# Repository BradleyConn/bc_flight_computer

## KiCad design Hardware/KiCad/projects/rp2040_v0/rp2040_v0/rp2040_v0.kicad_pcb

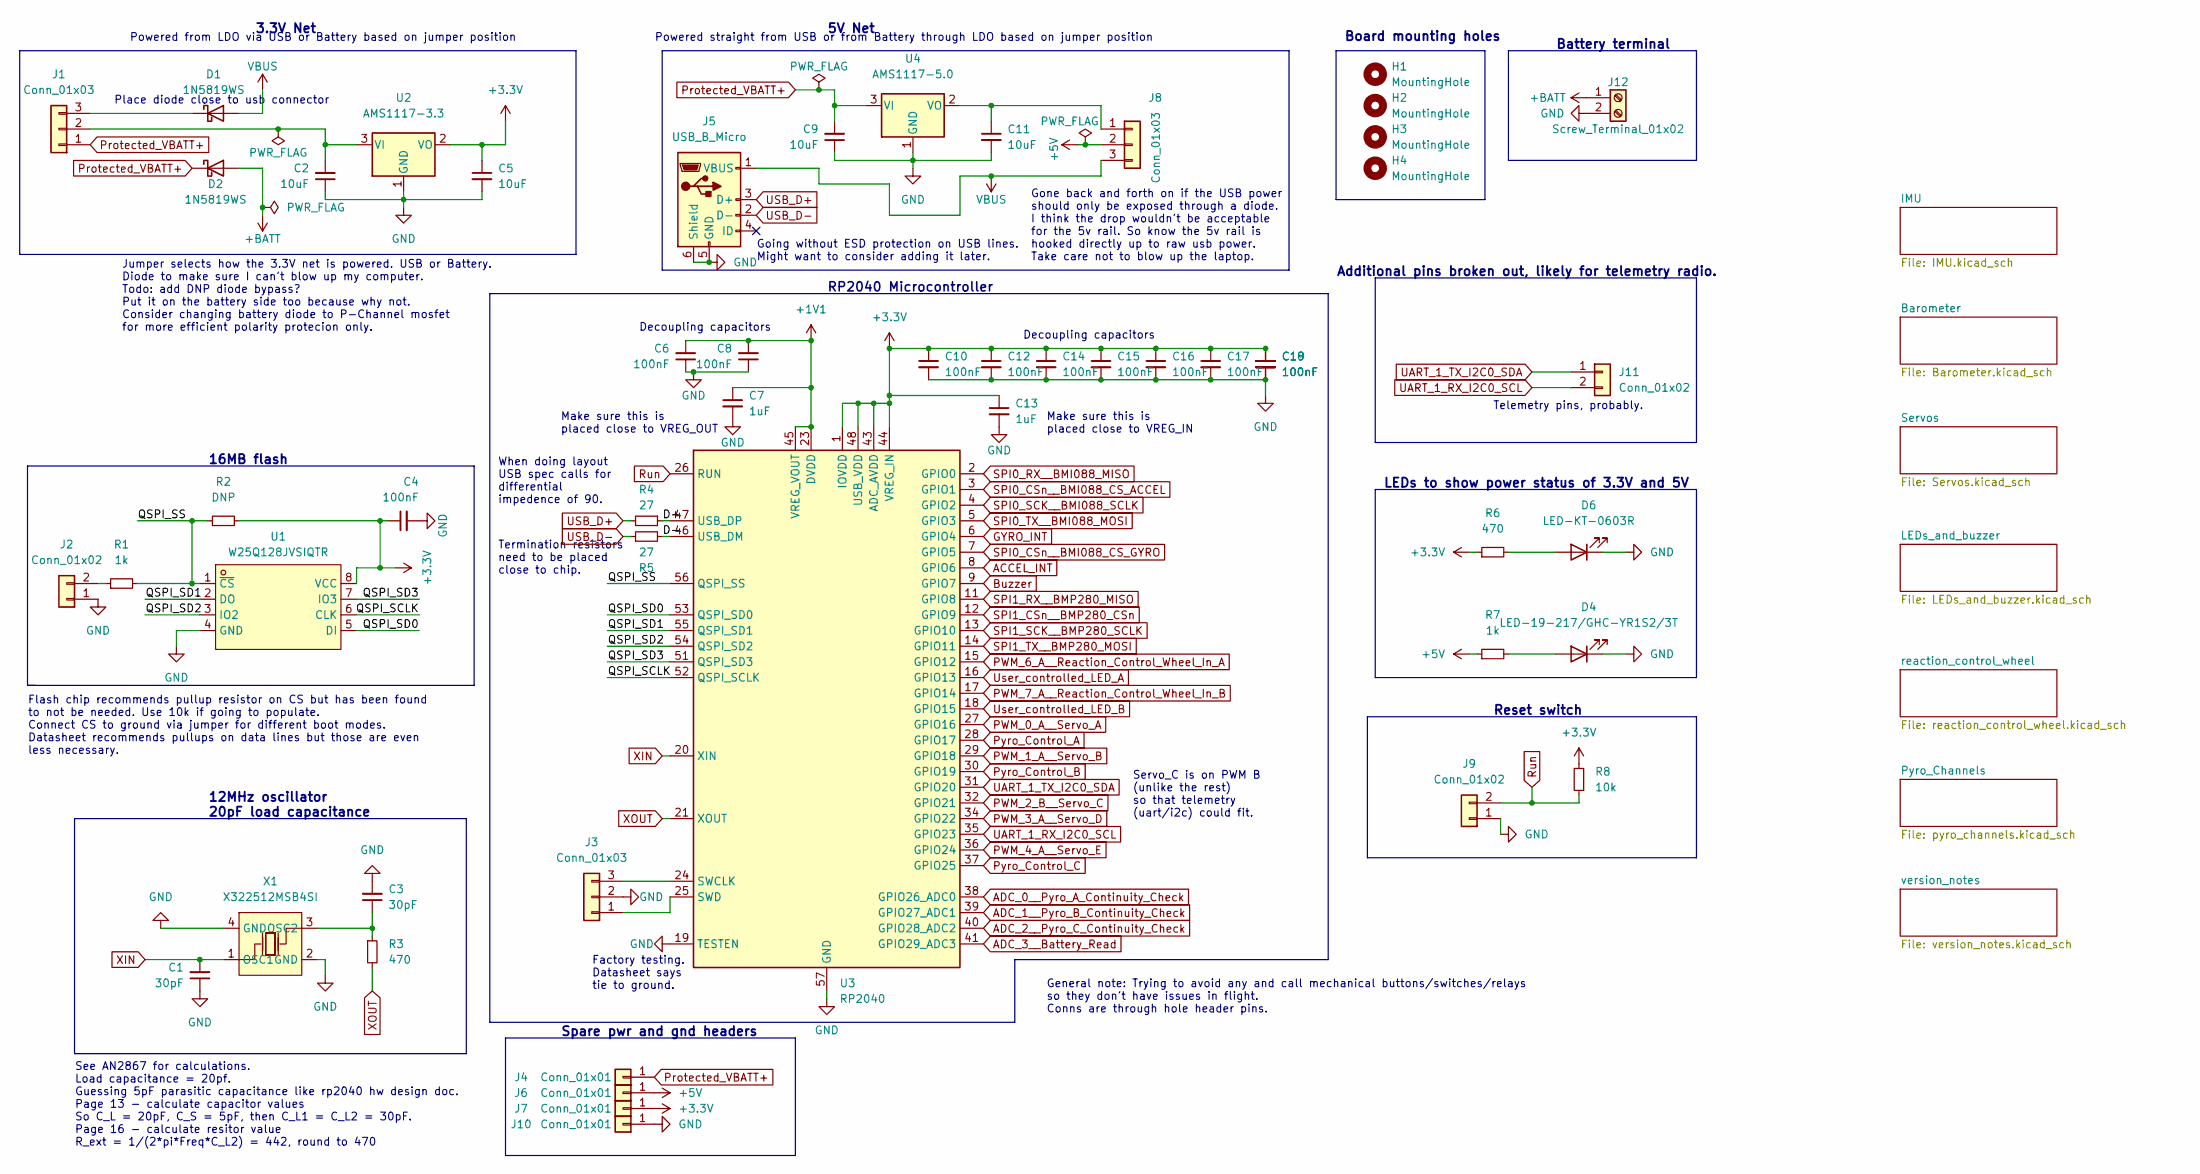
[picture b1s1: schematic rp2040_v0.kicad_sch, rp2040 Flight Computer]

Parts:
C1, C3: 30pF; C_0402_1005Metric; LCSC Part C1570
C2, C5, C9, C11: 10uF; C_0805_2012Metric; LCSC Part C15850
C4, C6, C8, C10, C12, C14, C15, C16, C17, C18, C19: 100nF; C_0402_1005Metric; LCSC Part C307331
C7, C13: 1uF; C_0402_1005Metric; LCSC Part C52923
D1, D2: 1N5819WS; D_SOD-323; LCSC Part C191023
D4: LED-19-217/GHC-YR1S2/3T; LED_0603_1608Metric; LCSC Part C72043
D6: LED-KT-0603R; LED_0603_1608Metric; LCSC Part C2286
H1, H2, H3, H4: MountingHole; MountingHole_2mm
J1, J3, J8: Conn_01x03; PinHeader_1x03_P2.54mm_Vertical
J2, J9, J11: Conn_01x02; PinHeader_1x02_P2.54mm_Vertical
J4, J6, J7, J10: Conn_01x01; PinHeader_1x01_P2.54mm_Vertical
J5: USB_B_Micro; MICRO-USB-SMD_MICROXNJ; LCSC Part C404969
J12: Screw_Terminal_01x02; CONN-TH_XY301V-A-5.0-2P; JLC Part Extended Part
R1, R7: 1k; R_0402_1005Metric; LCSC Part C11702
R2: DNP; R_0402_1005Metric
R3, R6: 470; R_0402_1005Metric; LCSC Part C25117
R4, R5: 27; R_0603_1608Metric; LCSC Part C25190
R8: 10k; R_0402_1005Metric; LCSC Part C25744
U1: W25Q128JVSIQTR; SOIC-8_5.23x5.23mm_P1.27mm; LCSC Part C97521
U2: AMS1117-3.3; SOT-223-3_TabPin2; LCSC Part C6186
U3: RP2040; LQFN-56_L7.0-W7.0-P0.4-EP; JLC Part Extended Part
U4: AMS1117-5.0; SOT-223-3_TabPin2; LCSC Part C6187
X1: X322512MSB4SI; OSC-SMD_4P-L3.2-W2.5-BL; LCSC Part C9002

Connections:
+1V1: C6.2, C7.1, C8.2, U3.23 (DVDD), U3.45 (VREG_VOUT), U3.50 (DVDD)
+3.3V: C4.1, C5.1, C10.1, C12.1, C13.1, C14.1, C15.1, C16.1, C17.1, C18.1, C19.1, J7.1, R2.2, R6.1, R8.2, U1.8 (VCC), U2.2 (VO), U3.1 (IOVDD), U3.10 (IOVDD), U3.22 (IOVDD), U3.33 (IOVDD), U3.42 (IOVDD), U3.43 (ADC_AVDD), U3.44 (VREG_IN), U3.48 (USB_VDD), U3.49 (IOVDD); also elsewhere on the board
+5V: J6.1, J8.2, R7.1; also elsewhere on the board
+BATT: D2.2 (A), J12.1; also elsewhere on the board
/D+: R4.1, U3.47 (USB_DP)
/D-: R5.2, U3.46 (USB_DM)
/QSPI_SCLK: U1.6 (CLK), U3.52 (QSPI_SCLK)
/QSPI_SD0: U1.5 (DI), U3.53 (QSPI_SD0)
/QSPI_SD1: U1.2 (DO), U3.55 (QSPI_SD1)
/QSPI_SD2: U1.3 (IO2), U3.54 (QSPI_SD2)
/QSPI_SD3: U1.7 (IO3), U3.51 (QSPI_SD3)
/QSPI_SS: R1.2, R2.1, U1.1 (~CS), U3.56 (QSPI_SS)
ACCEL_INT: U3.8 (GPIO6); also elsewhere on the board
ADC_0__Pyro_A_Continuity_Check: U3.38 (GPIO26_ADC0); also elsewhere on the board
ADC_1__Pyro_B_Continuity_Check: U3.39 (GPIO27_ADC1); also elsewhere on the board
ADC_2__Pyro_C_Continuity_Check: U3.40 (GPIO28_ADC2); also elsewhere on the board
ADC_3__Battery_Read: U3.41 (GPIO29_ADC3); also elsewhere on the board
Buzzer: U3.9 (GPIO7); also elsewhere on the board
GND: C1.1, C2.1, C3.2, C4.2, C5.2, C6.1, C7.2, C8.1, C9.1, C10.2, C11.2, C12.2, C13.2, C14.2, C15.2, C16.2, C17.2, C18.2, C19.2, D4.1 (K), D6.1 (K), J2.1, J3.2, J5.5 (GND), J5.6 (Shield), J9.1, J10.1, J12.2, U1.4 (GND), U2.1 (GND), U3.19 (TESTEN), U3.57 (GND), U4.1 (GND), X1.2 (GND), X1.4 (GND); also elsewhere on the board
GYRO_INT: U3.6 (GPIO4); also elsewhere on the board
unnamed: C2.2, J1.2, U2.3 (VI)
unnamed: C3.1, R3.1, X1.3 (OSC2)
unnamed: C11.1, J8.1, U4.2 (VO)
unnamed: D1.1 (K), J1.3
unnamed: D4.2 (A), R7.2
unnamed: D6.2 (A), R6.2
unnamed: J2.2, R1.1
unnamed: J3.1, U3.25 (SWD)
unnamed: J3.3, U3.24 (SWCLK)
PWM_0_A__Servo_A: U3.27 (GPIO16); also elsewhere on the board
PWM_1_A__Servo_B: U3.29 (GPIO18); also elsewhere on the board
PWM_2_B__Servo_C: U3.32 (GPIO21); also elsewhere on the board
PWM_3_A__Servo_D: U3.34 (GPIO22); also elsewhere on the board
PWM_4_A__Servo_E: U3.36 (GPIO24); also elsewhere on the board
PWM_6_A__Reaction_Control_Wheel_In_A: U3.15 (GPIO12); also elsewhere on the board
PWM_7_A__Reaction_Control_Wheel_In_B: U3.17 (GPIO14); also elsewhere on the board
Protected_VBATT+: C9.2, D2.1 (K), J1.1, J4.1, U4.3 (VI); also elsewhere on the board
Pyro_Control_A: U3.28 (GPIO17); also elsewhere on the board
Pyro_Control_B: U3.30 (GPIO19); also elsewhere on the board
Pyro_Control_C: U3.37 (GPIO25); also elsewhere on the board
Run: J9.2, R8.1, U3.26 (RUN)
SPI0_CSn__BMI088_CS_ACCEL: U3.3 (GPIO1); also elsewhere on the board
SPI0_CSn__BMI088_CS_GYRO: U3.7 (GPIO5); also elsewhere on the board
SPI0_RX__BMI088_MISO: U3.2 (GPIO0); also elsewhere on the board
SPI0_SCK__BMI088_SCLK: U3.4 (GPIO2); also elsewhere on the board
SPI0_TX__BMI088_MOSI: U3.5 (GPIO3); also elsewhere on the board
SPI1_CSn__BMP280_CSn: U3.12 (GPIO9); also elsewhere on the board
SPI1_RX__BMP280_MISO: U3.11 (GPIO8); also elsewhere on the board
SPI1_SCK__BMP280_SCLK: U3.13 (GPIO10); also elsewhere on the board
SPI1_TX__BMP280_MOSI: U3.14 (GPIO11); also elsewhere on the board
UART_1_RX_I2C0_SCL: J11.2, U3.35 (GPIO23)
UART_1_TX_I2C0_SDA: J11.1, U3.31 (GPIO20)
USB_D+: J5.3 (D+), R4.2
USB_D-: J5.2 (D-), R5.1
User_controlled_LED_A: U3.16 (GPIO13); also elsewhere on the board
User_controlled_LED_B: U3.18 (GPIO15); also elsewhere on the board
VBUS: D1.2 (A), J5.1 (VBUS), J8.3
XIN: C1.2, U3.20 (XIN), X1.1 (OSC1)
XOUT: R3.2, U3.21 (XOUT)

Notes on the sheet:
Jumper selects how the 3.3V net is powered. USB or Battery. Diode to make sure I can't blow up my computer. Todo: add DNP diode bypass? Put it on the battery side too because why not. Consider changing battery diode to P-Channel mosfet for more efficient polarity protecion only.
Termination resistors need to be placed close to chip.
Telemetry pins, probably.
Make sure this is placed close to VREG_OUT
Servo_C is on PWM B (unlike the rest) so that telemetry (uart/i2c) could fit.
Flash chip recommends pullup resistor on CS but has been found to not be needed. Use 10k if going to populate. Connect CS to ground via jumper for different boot modes. Datasheet recommends pullups on data lines but those are even less necessary.
Factory testing. Datasheet says tie to ground.
3.3V Net
16MB flash
Board mounting holes
Battery terminal
Additional pins broken out, likely for telemetry radio.
Reset switch
When doing layout USB spec calls for differential impedence of 90.
Make sure this is placed close to VREG_IN
Gone back and forth on if the USB power should only be exposed through a diode. I think the drop wouldn't be acceptable for the 5v rail. So know the 5v rail is hooked directly up to raw usb power. Take care not to blow up the laptop.
Place diode close to usb connector
See AN2867 for calculations. Load capacitance = 20pf. Guessing 5pF parasitic capacitance like rp2040 hw design doc. Page 13 - calculate capacitor values So C_L = 20pF, C_S = 5pF, then C_L1 = C_L2 = 30pF. Page 16 - calculate resitor value R_ext = 1/(2*pi*Freq*C_L2) = 442, round to 470
5V Net
Going without ESD protection on USB lines. Might want to consider adding it later.
RP2040 Microcontroller
General note: Trying to avoid any and call mechanical buttons/switches/relays so they don't have issues in flight. Conns are through hole header pins.
Spare pwr and gnd headers
Powered straight from USB or from Battery through LDO based on jumper position
Decoupling capacitors
Powered from LDO via USB or Battery based on jumper position
12MHz oscillator 20pF load capacitance
LEDs to show power status of 3.3V and 5V

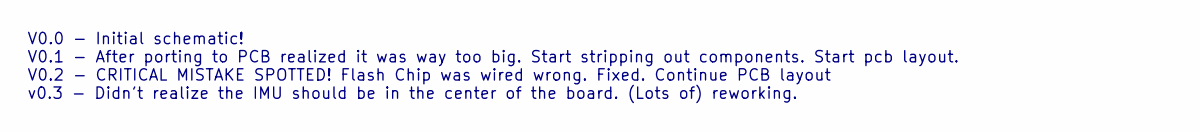
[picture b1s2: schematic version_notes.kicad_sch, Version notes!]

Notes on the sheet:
V0.0 - Initial schematic! V0.1 - After porting to PCB realized it was way too big. Start stripping out components. Start pcb layout. V0.2 - CRITICAL MISTAKE SPOTTED! Flash Chip was wired wrong. Fixed. Continue PCB layout v0.3 - Didn't realize the IMU should be in the center of the board. (Lots of) 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

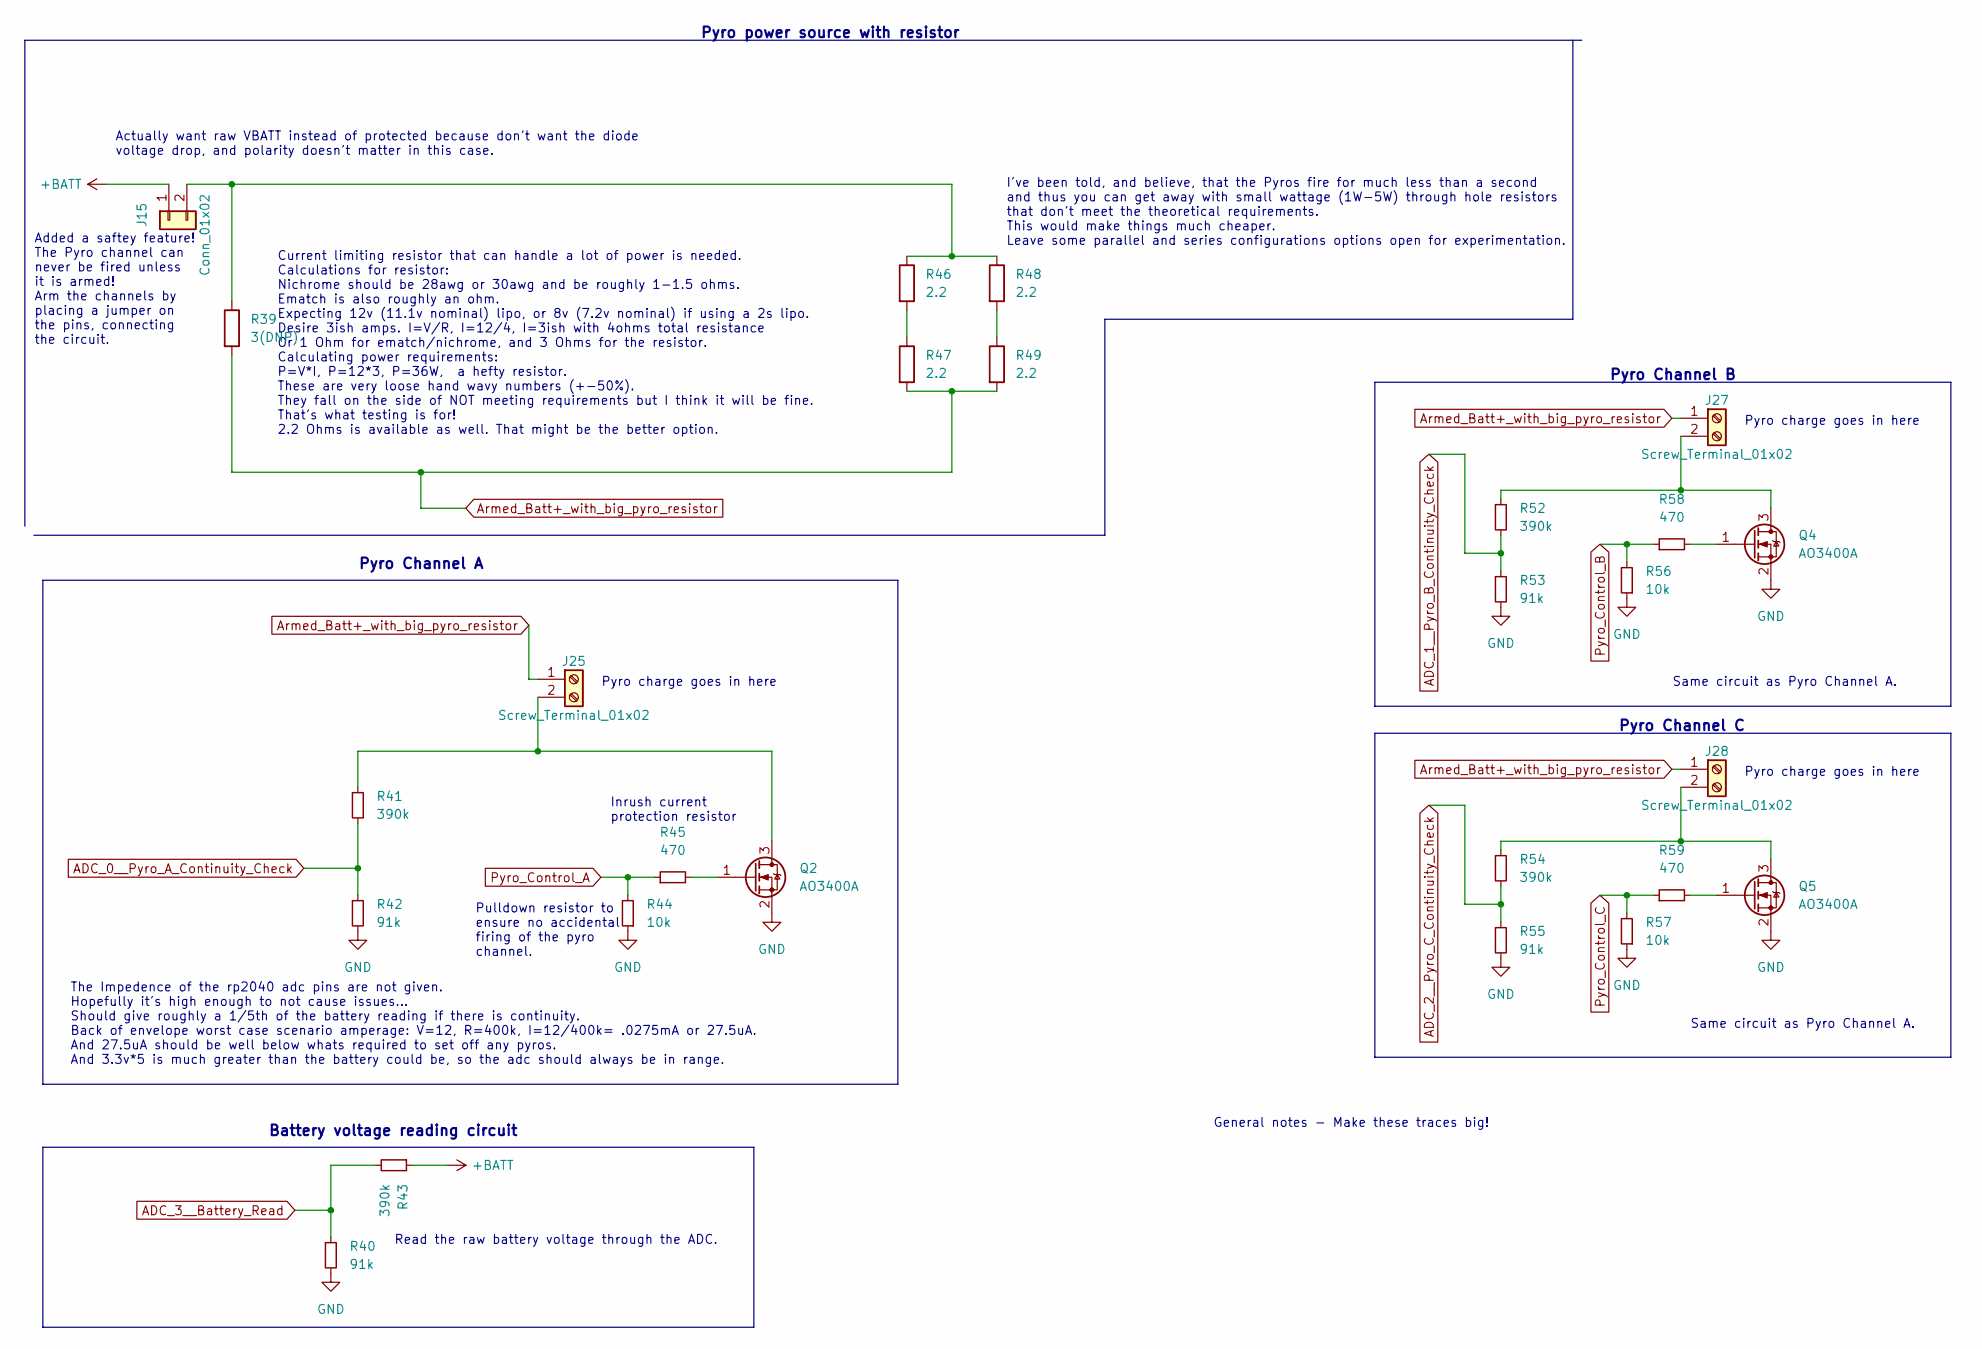
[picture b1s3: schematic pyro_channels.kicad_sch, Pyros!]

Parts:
J15: Conn_01x02; PinHeader_1x02_P2.54mm_Vertical
J25, J27, J28: Screw_Terminal_01x02; CONN-TH_XY301V-A-5.0-2P; JLC Part Extended Part
Q2, Q4, Q5: AO3400A; SOT-23; LCSC Part C20917
R39: 3(DNP); TO-263-2_TabPin1
R40, R42, R53, R55: 91k; R_0402_1005Metric; LCSC Part C25741
R41, R43, R52, R54: 390k; R_0603_1608Metric; LCSC Part C23150
R44, R56, R57: 10k; R_0402_1005Metric; LCSC Part C25744
R45, R58, R59: 470; R_0402_1005Metric; LCSC Part C25117
R46, R47, R48, R49: 2.2; R_Axial_DIN0309_L9.0mm_D3.2mm_P12.70mm_Horizontal; JLC Part Basic Part

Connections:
+BATT: J15.1, R43.1; also elsewhere on the board
ADC_0__Pyro_A_Continuity_Check: R41.2, R42.1; also elsewhere on the board
ADC_1__Pyro_B_Continuity_Check: R52.2, R53.1; also elsewhere on the board
ADC_2__Pyro_C_Continuity_Check: R54.2, R55.1; also elsewhere on the board
ADC_3__Battery_Read: R40.1, R43.2; also elsewhere on the board
Armed_Batt+_with_big_pyro_resistor: J25.1, J27.1, J28.1, R39.2, R47.2, R49.2
GND: Q2.2 (S), Q4.2 (S), Q5.2 (S), R40.2, R42.2, R44.1, R53.2, R55.2, R56.1, R57.1; also elsewhere on the board
unnamed: J15.2, R39.1, R46.1, R48.1
unnamed: J25.2, Q2.3 (D), R41.1
unnamed: J27.2, Q4.3 (D), R52.1
unnamed: J28.2, Q5.3 (D), R54.1
unnamed: Q2.1 (G), R45.2
unnamed: Q4.1 (G), R58.2
unnamed: Q5.1 (G), R59.2
unnamed: R46.2, R47.1
unnamed: R48.2, R49.1
Pyro_Control_A: R44.2, R45.1; also elsewhere on the board
Pyro_Control_B: R56.2, R58.1; also elsewhere on the board
Pyro_Control_C: R57.2, R59.1; also elsewhere on the board

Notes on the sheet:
Current limiting resistor that can handle a lot of power is needed. Calculations for resistor: Nichrome should be 28awg or 30awg and be roughly 1-1.5 ohms. Ematch is also roughly an ohm. Expecting 12v (11.1v nominal) lipo, or 8v (7.2v nominal) if using a 2s lipo. Desire 3ish amps. I=V/R, I=12/4, I=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
Added a saftey feature! The Pyro channel can never be fired unless it is armed! Arm the channels by placing a jumper on the pins, connecting the circuit.
Pyro Channel A
Pyro Channel C
Pyro charge goes in here
Pyro Channel B
The Impedence of the rp2040 adc pins are not given. Hopefully it's high enough to not cause issues... Should give roughly a 1/5th of the battery reading if there is continuity. Back of envelope worst case scenario amperage: V=12, R=400k, I=12/400k= .0275mA or 27.5uA. And 27.5uA should be well below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
Inrush current protection resistor
Actually want raw VBATT instead of protected because don't want the diode voltage drop, and polarity doesn't matter in this case.
Battery voltage reading circuit
Pyro power source with resistor
Same circuit as Pyro Channel A.
Read the raw battery voltage through the ADC.
I've been told, and believe, that the Pyros fire for much less than a second and thus you can get away with small wattage (1W-5W) through hole resistors that don't meet the theoretical requirements. This would make things much cheaper. Leave some parallel and series configurations options open for 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
General notes - Make these traces big!
Pulldown resistor to ensure no accidental firing of the pyro channel.

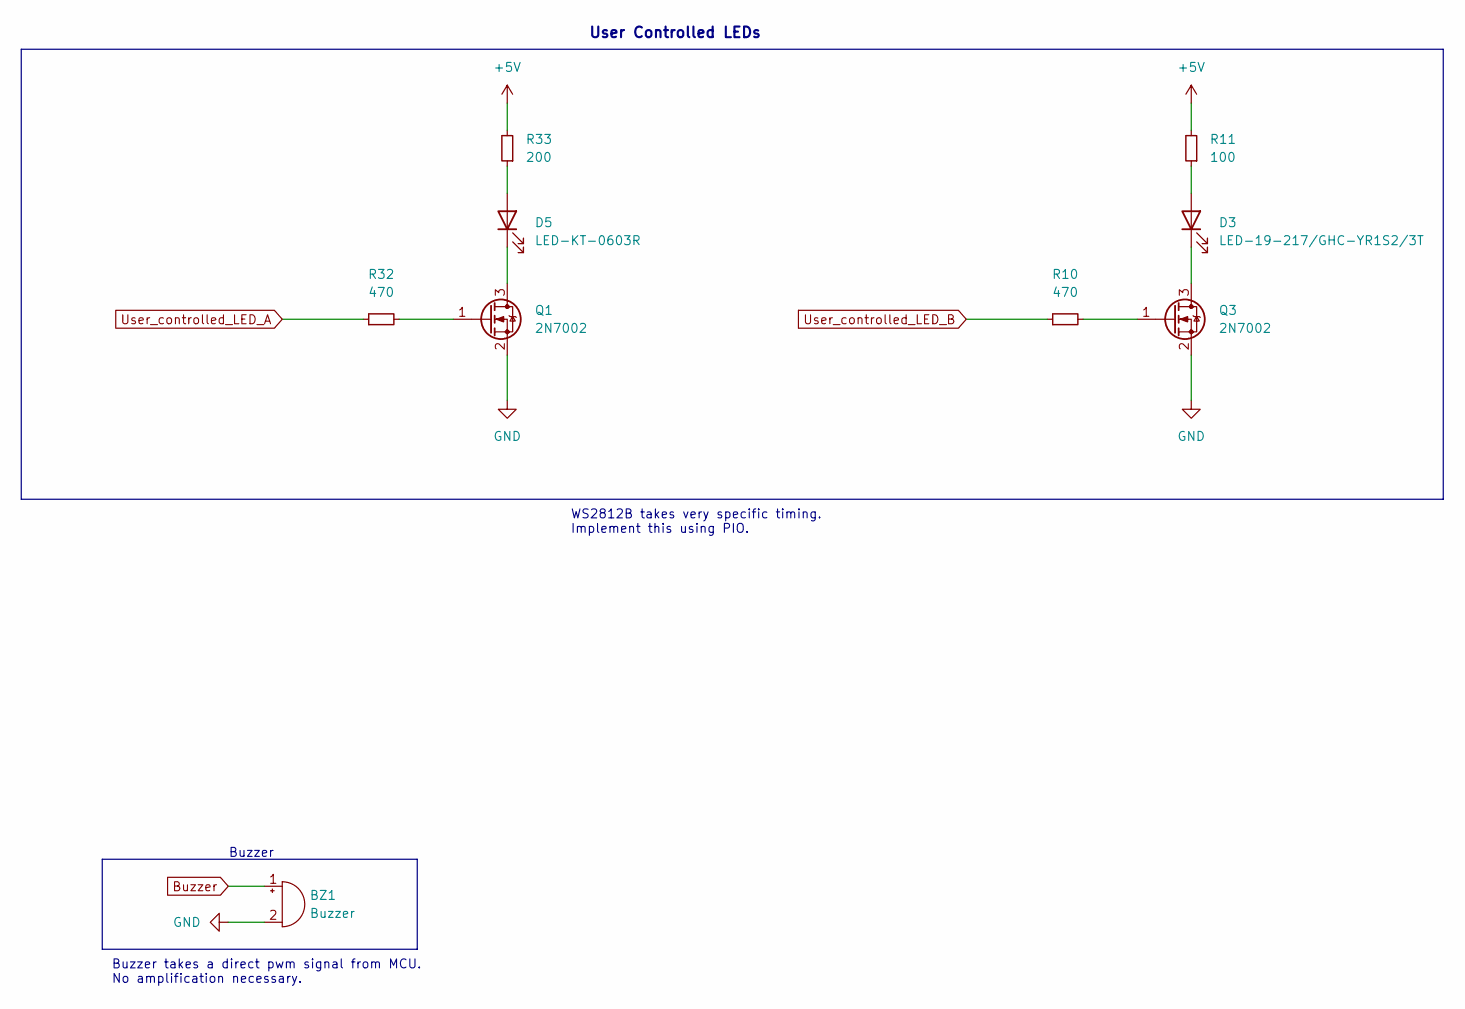
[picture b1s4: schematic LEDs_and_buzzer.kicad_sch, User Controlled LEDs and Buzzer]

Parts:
BZ1: Buzzer; BUZ-TH_BD9.0-P4.00-D0.6-FD; LCSC Part C161819
D3: LED-19-217/GHC-YR1S2/3T; LED_0603_1608Metric; LCSC Part C72043
D5: LED-KT-0603R; LED_0603_1608Metric; LCSC Part C2286
Q1, Q3: 2N7002; SOT-23; LCSC Part C8545
R10, R32: 470; R_0402_1005Metric; LCSC Part C25117
R11: 100; R_0402_1005Metric; LCSC Part C25076
R33: 200; R_0402_1005Metric; LCSC Part C25087

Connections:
+5V: R11.2, R33.2; also elsewhere on the board
Buzzer: BZ1.1 (-); also elsewhere on the board
GND: BZ1.2 (+), Q1.2 (S), Q3.2 (S); also elsewhere on the board
unnamed: D3.1 (K), Q3.3 (D)
unnamed: D3.2 (A), R11.1
unnamed: D5.1 (K), Q1.3 (D)
unnamed: D5.2 (A), R33.1
unnamed: Q1.1 (G), R32.2
unnamed: Q3.1 (G), R10.2
User_controlled_LED_A: R32.1; also elsewhere on the board
User_controlled_LED_B: R10.1; also elsewhere on the board

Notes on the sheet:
Buzzer takes a direct pwm signal from MCU. No amplification necessary.
WS2812B takes very specific timing. Implement this using PIO.
Buzzer
User Controlled LEDs

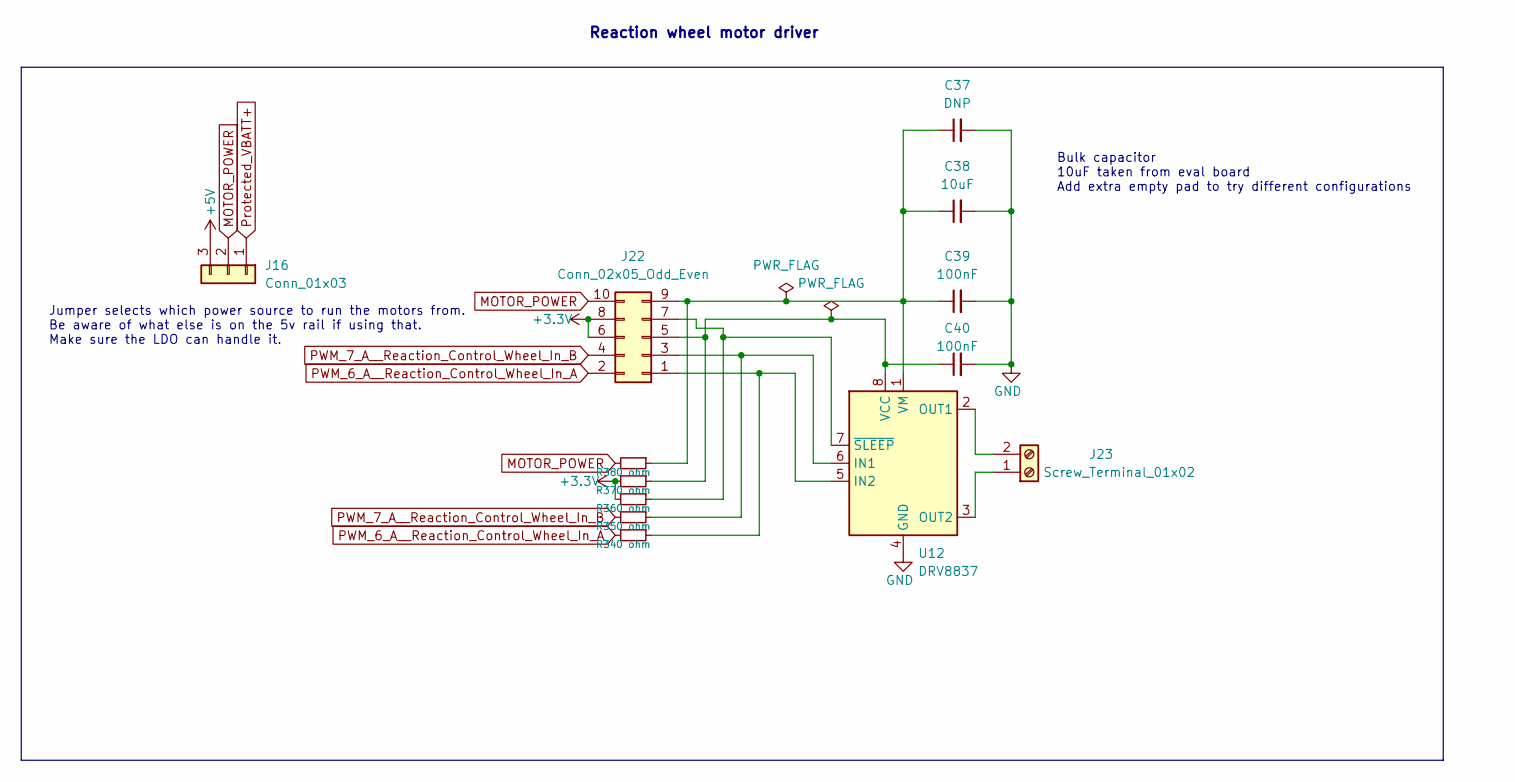
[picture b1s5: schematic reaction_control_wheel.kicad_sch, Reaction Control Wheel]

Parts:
C37: DNP; C_0603_1608Metric
C38: 10uF; C_0805_2012Metric; LCSC Part C15850
C39, C40: 100nF; C_0402_1005Metric; LCSC Part C307331
J16: Conn_01x03; PinHeader_1x03_P2.54mm_Vertical
J22: Conn_02x05_Odd_Even; PinHeader_2x05_P2.54mm_Vertical
J23: Screw_Terminal_01x02; CONN-TH_XY301V-A-5.0-2P; JLC Part Extended Part
R34, R35, R36, R37, R38: 0 ohm; R_0402_1005Metric; LCSC Part C17168
U12: DRV8837; WSON-8-1EP_2x2mm_P0.5mm_EP0.9x1.6mm; LCSC Part C39159

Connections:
+3.3V: J22.6, J22.8, R36.2, R37.2; also elsewhere on the board
+5V: J16.3; also elsewhere on the board
GND: C37.2, C38.2, C39.2, C40.2, U12.4 (GND), U12.9 (GND); also elsewhere on the board
MOTOR_POWER: J16.2, J22.10, R38.2
unnamed: C37.1, C38.1, C39.1, J22.9, R38.1, U12.1 (VM)
unnamed: C40.1, J22.5, R37.1, U12.8 (VCC)
unnamed: J22.1, R34.1, U12.5 (IN2)
unnamed: J22.3, R35.1, U12.6 (IN1)
unnamed: J22.7, R36.1, U12.7 (~SLEEP)
unnamed: J23.1, U12.3 (OUT2)
unnamed: J23.2, U12.2 (OUT1)
PWM_6_A__Reaction_Control_Wheel_In_A: J22.2, R34.2; also elsewhere on the board
PWM_7_A__Reaction_Control_Wheel_In_B: J22.4, R35.2; also elsewhere on the board
Protected_VBATT+: J16.1; also elsewhere on the board

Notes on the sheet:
Reaction wheel motor driver
Bulk capacitor 10uF taken from eval board Add extra empty pad to try different configurations
Jumper selects which power source to run the motors from. Be aware of what else is on the 5v rail if using that. Make sure the LDO can handle it.

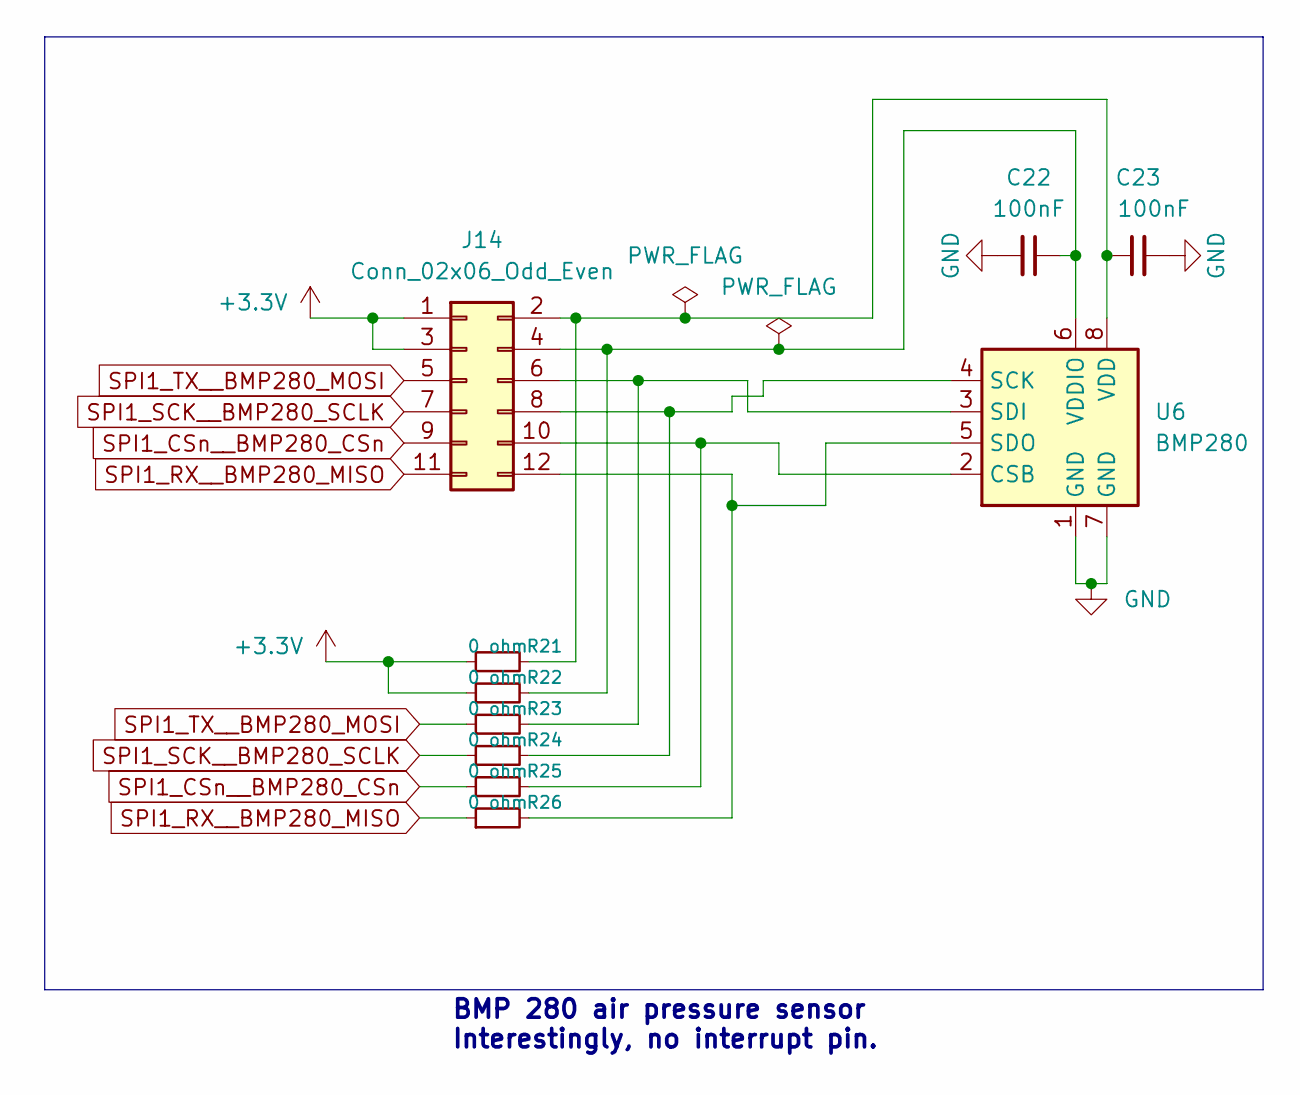
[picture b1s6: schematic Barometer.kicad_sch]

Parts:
C22, C23: 100nF; C_0402_1005Metric; LCSC Part C307331
J14: Conn_02x06_Odd_Even; PinHeader_2x06_P2.54mm_Vertical
R21, R22, R23, R24, R25, R26: 0 ohm; R_0402_1005Metric; LCSC Part C17168
U6: BMP280; Bosch_LGA-8_2x2.5mm_P0.65mm_ClockwisePinNumbering; LCSC Part C83291

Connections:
+3.3V: J14.1, J14.3, R21.1, R22.1; also elsewhere on the board
GND: C22.2, C23.2, U6.1 (GND), U6.7 (GND); also elsewhere on the board
unnamed: C22.1, J14.4, R22.2, U6.6 (VDDIO)
unnamed: C23.1, J14.2, R21.2, U6.8 (VDD)
unnamed: J14.6, R23.2, U6.3 (SDI)
unnamed: J14.8, R24.2, U6.4 (SCK)
unnamed: J14.10, R25.2, U6.2 (CSB)
unnamed: J14.12, R26.2, U6.5 (SDO)
SPI1_CSn__BMP280_CSn: J14.9, R25.1; also elsewhere on the board
SPI1_RX__BMP280_MISO: J14.11, R26.1; also elsewhere on the board
SPI1_SCK__BMP280_SCLK: J14.7, R24.1; also elsewhere on the board
SPI1_TX__BMP280_MOSI: J14.5, R23.1; also elsewhere on the board

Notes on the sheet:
BMP 280 air pressure sensor Interestingly, no interrupt pin.

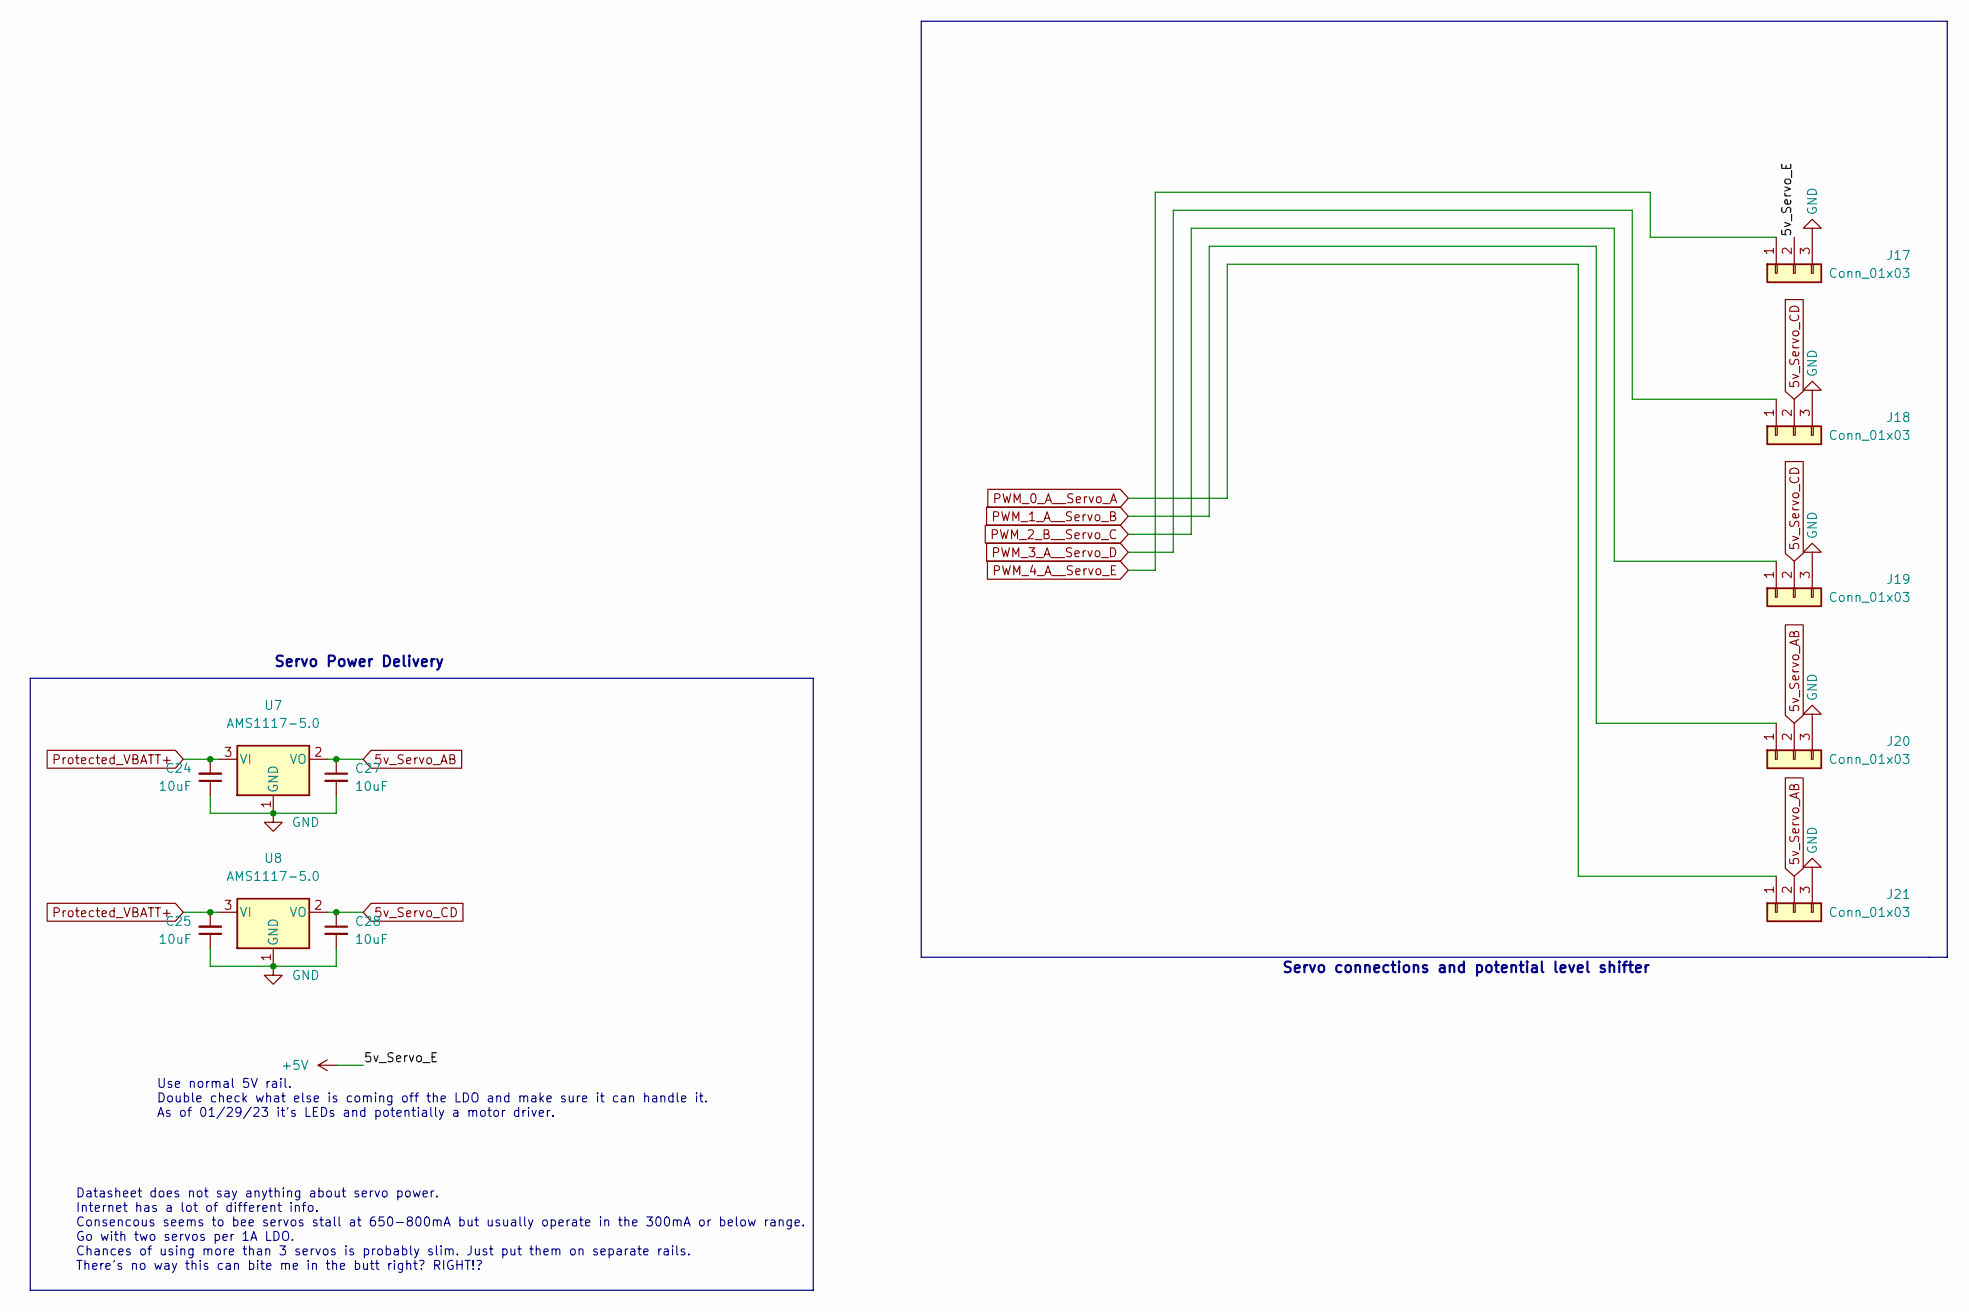
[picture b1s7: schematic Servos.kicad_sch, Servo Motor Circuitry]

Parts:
C24, C25, C27, C28: 10uF; C_0805_2012Metric; LCSC Part C15850
J17, J18, J19, J20, J21: Conn_01x03; PinHeader_1x03_P2.54mm_Vertical
U7, U8: AMS1117-5.0; SOT-223-3_TabPin2; LCSC Part C6187

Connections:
5v_Servo_AB: C27.1, J20.2, J21.2, U7.2 (VO)
5v_Servo_CD: C28.1, J18.2, J19.2, U8.2 (VO)
+5V: J17.2; also elsewhere on the board
GND: C24.1, C25.1, C27.2, C28.2, J17.3, J18.3, J19.3, J20.3, J21.3, U7.1 (GND), U8.1 (GND); also elsewhere on the board
PWM_0_A__Servo_A: J21.1; also elsewhere on the board
PWM_1_A__Servo_B: J20.1; also elsewhere on the board
PWM_2_B__Servo_C: J19.1; also elsewhere on the board
PWM_3_A__Servo_D: J18.1; also elsewhere on the board
PWM_4_A__Servo_E: J17.1; also elsewhere on the board
Protected_VBATT+: C24.2, C25.2, U7.3 (VI), U8.3 (VI); also elsewhere on the board

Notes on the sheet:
Servo Power Delivery
Datasheet does not say anything about servo power. Internet has a lot of different info. Consencous seems to bee servos stall at 650-800mA but usually operate in the 300mA or below range. Go with two servos per 1A LDO. Chances of using more than 3 servos is probably slim. Just put them on separate 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
Servo connections and potential level shifter
Use normal 5V rail. Double check what else is coming off the LDO and make sure it can handle it. As of 01/29/23 it's LEDs and potentially a motor driver.
